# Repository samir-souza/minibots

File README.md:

</img><br> 

**minibots** is an open source and open hardware platform for experimenting with autonomous bots, Machine Learning and Programming. You can download the code and the assets to create your own fleet of bots, using a 3D printer and some basic electronic components. It is based on the ESP8266 uController, but you can modify it and use any uController you want. 
 
<br><br> 

<p align="center">
</img>
</p>

## Smart City with minibots
In this repo you will find a demo of a Smart City simulation. The idea of this demo is to use **minibots** to 
represent cars moving around on the streets of a city. There are a few places around the track like: houses, gas stations, buildings, etc.
The cars are going from on place to another, simulating a rush hour and generting traffic jams. The targets are selected randomly, and
each car automatically selects the next random target as soon as it gets to the current target place. The controller will try to 
re-route the cars to alternative paths to alleviate the traffic. You can also make the things worse by manually adding some 
obstacles to the streets, like: dogs, pedestriang, etc.
Also, there is a special marker that you can put close to a place. It will bias the next target selected by the first car that finishes the current path.  

<p align="center">
 </img>
</p> 

[Click here for more details about this demo](04_Examples/01_SmartCity)

## Components

A Minibot is composed by three modules: 1) the 3D printed parts and a few other parts; 2) the bot Printed Circuit Board (PCB); and 3) the firmware;

### 3D Models
In the first module [3D Models](01_3DModels) you will find the STL files and the FreeCAD projects used to build this project. Just follow the instructions on the module page "[3D Models](01_3DModels)" to get the files and print them.
### Bot PCB
In the second module [Bot PCB](02_BotPCB) you will find instructions about how to create the Printed Circuit Board for your Minibot. Also, you'll find the [Gerber files](https://en.wikipedia.org/wiki/Gerber_format), required for manufacturing the PCB and the components list.
### Firmware
In the third module [Firmware](03_BotFirmware) you will find the binary images and a Dockerfile that you can use to hack and customize the firmware of your Minibot. The firmware is for the uController ESP8266 and is based on Nodemcu LUA: https://nodemcu.readthedocs.io/en/master/. So, after installing the Nodemcu firmware you can customize the Lua scripts to adapt your Minibot to any project.

## Assembling
Click on [ASSEMBLING](ASSEMBLING.md) to see the instructions of how to create your own Minibot from scratch.

# License
The 3D Models and the PCB projects are released in Creative Commons Attribution-ShareAlike 4.0 License and the source code available in this repository is licensed under the GNU General Public License v3.0.

----
<div>Logo created by <a href="https://www.designevo.com/logo-maker/" title="Free Online Logo Maker">DesignEvo logo maker</a></div>

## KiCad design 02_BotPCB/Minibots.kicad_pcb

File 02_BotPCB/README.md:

## Preparing the PCB

Minibots is based on a very popular and cheap uController, the . So, the PCB is basically this uController connected to two servos (controlled by PWM) and other elements, like the classic accelerometer+gyroscope MPU6050, external pins, control LED, etc.

The PCB was created with  **v4.0.2+dfsg1-stable** and you can see the KiCad project in this directory. The Gerber files can also be found in this dir. In order to manufacture a new PCB for you Minibot, you can use the Gerber files. If you never created a PCB before, you can use some online services that you just upload the Gerber files, pay for the boards and you then receive the boards at your home. The project is very simple. It has just one layer and you can make tracks with **copper 2Oz**.

<table>
  <tr>
    <td>PCB Layout</td>
    <td>Connections</td>
    <td>Top</td>
    <td>Bottom</td>
  </tr>
  <tr>
    <td></img></td>
    <td></img></td>
    <td></img></td>
    <td></img></td>
  </tr>
</table>

As you can see above, the layout is very simple and the list of components (BOM) is:
 - D1: LED-3MM
 - P1: Pin_Header_Straight_1x03 ; LeftServo (Micro Servo 9g SG90 with 360o hack)
 - P2: Pin_Header_Straight_1x03 ; RightServo (Micro Servo 9g SG90 with 360o hack)
 - P4: Pin_Header_Straight_1x01 ; Antenna
 - P5: Pin_Header_Straight_1x03 ; Serial
 - SW1: MiniSlideSwitch ; [Switch specs](imgs/mini_switch.jpg)
 - U1: MPU6050 ; MPU6050
 - C1,C2: C_0805_HandSoldering ; 10uf
 - C3: C_0805_HandSoldering ; 1uf
 - R2: R_0805_HandSoldering ; 100k
 - U3: MSOP-8_3x3mm_Pitch0.65mm ; MCP1253
 - R1: R_0805_HandSoldering ; 100
 - P6: Pin_Header_Straight_1x02 ; VCC
 - P7: Pin_Header_Straight_1x02 ; Power
 - P3: Pin_Header_Straight_1x02 ; Flash/Ext
 - U2: ESP8266-06
 
 ### Considerations
 You need to have some soldering skills to put all the components on the board. The uController requires an SMD soldering station, but the rest of the components can be soldered by just using a normal iron.
 
 **Micro Servo 9g SG90** is a 180 degrees servo. You need to hack it to transform it into a continuous servo (360 degrees). There are tons of tutorials on the Internet teaching how to do that. Here it is an example: https://rookieelectronics.com/servohack/
 
 **MCP1253** is a power pump, it improves the battery energy utilization and also works as a power regulation. It's mandatory to keep the correct voltage (3.3v) all the time to the uController. It also works as a power isolation, given the servos are connected directly to the battery and the rest of the circuit is feed by the power pump.
 
 **ESP8266** package 04 was used in the original project, but this packaging was discontinued, so, in v02 (this version) the package 06 was used. It is easier to find on the Internet but it is more difficult to be soldered, given it requires a Rework station (SMD soldering machine with hot air).
 
 **SMD** is important to keep the size of the board in general. You can see that all the resistors and capacitors are **SMD 0805**.

 Bottom view of the Minibot after finishing the assembly in the 3D printed Chassis:  
</img>

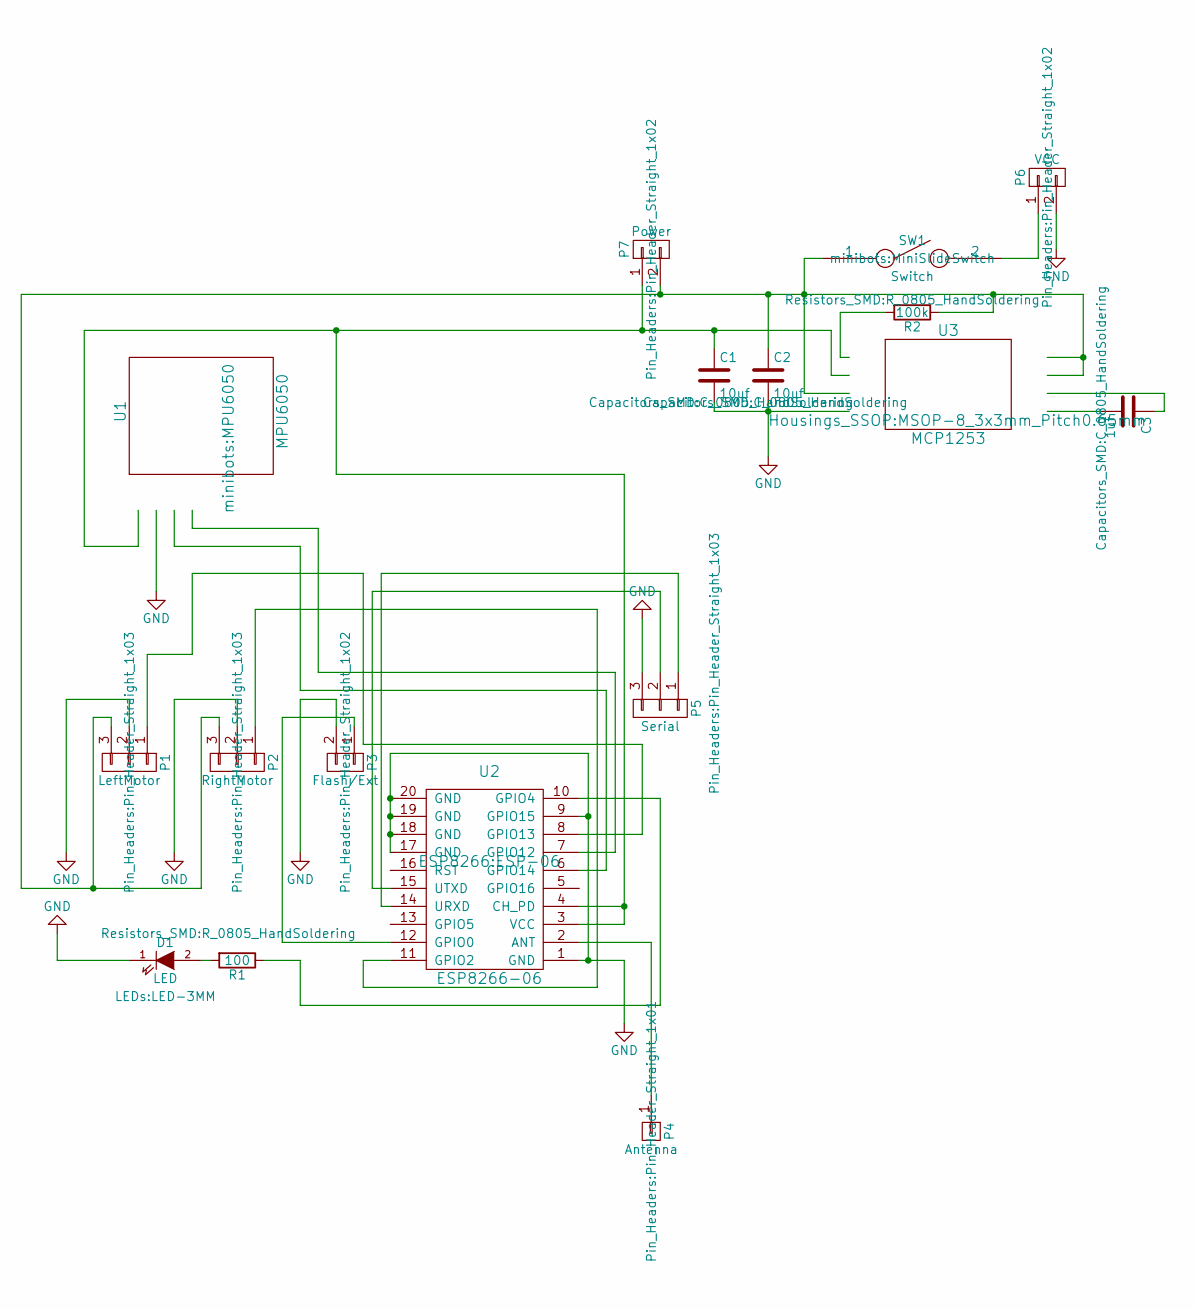
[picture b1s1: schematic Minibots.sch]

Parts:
C1, C2: 10uf; C_0805_HandSoldering
C3: 1uf; C_0805_HandSoldering
D1: LED; LED-3MM
P1: LeftMotor; Pin_Header_Straight_1x03
P2: RightMotor; Pin_Header_Straight_1x03
P3: Flash/Ext; Pin_Header_Straight_1x02
P4: Antenna; Pin_Header_Straight_1x01
P5: Serial; Pin_Header_Straight_1x03
P6: VCC; Pin_Header_Straight_1x02
P7: Power; Pin_Header_Straight_1x02
R1: 100; R_0805_HandSoldering
R2: 100k; R_0805_HandSoldering
SW1: Switch; MiniSlideSwitch
U1: MPU6050
U2: ESP8266-06; ESP-06
U3: MCP1253; MSOP-8_3x3mm_Pitch0.65mm

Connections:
GND: C1.2, C2.2, D1.1 (K), P1.2, P2.2, P3.2, P5.3, P6.2, U1.2 (GND), U2.1 (GND), U2.9 (GPIO15), U2.17 (GND), U2.18 (GND), U2.19 (GND), U2.20 (GND), U3.4 (GND)
unnamed: C1.1, P7.1, U1.1 (VCC), U2.3 (VCC), U2.4 (CH_PD), U3.2 (VOUT)
unnamed: C2.1, P1.3, P2.3, P7.2, R2.1, SW1.1, U3.3 (VIN), U3.7 (SHDN), U3.8 (SELECT)
unnamed: C3.1, U3.6 (C+)
unnamed: C3.2, U3.5 (C-)
unnamed: D1.2 (A), R1.2
unnamed: P1.1, U2.8 (GPIO13)
unnamed: P2.1, U2.11 (GPIO2)
unnamed: P3.1, U2.12 (GPIO0)
unnamed: P4.1, U2.2 (ANT)
unnamed: P5.1, U2.14 (URXD)
unnamed: P5.2, U2.15 (UTXD)
unnamed: P6.1, SW1.2
unnamed: R1.1, U2.10 (GPIO4)
unnamed: R2.2, U3.1 (PGOOD)
unnamed: U1.3 (SCL), U2.6 (GPIO14)
unnamed: U1.4 (SDA), U2.7 (GPIO12)

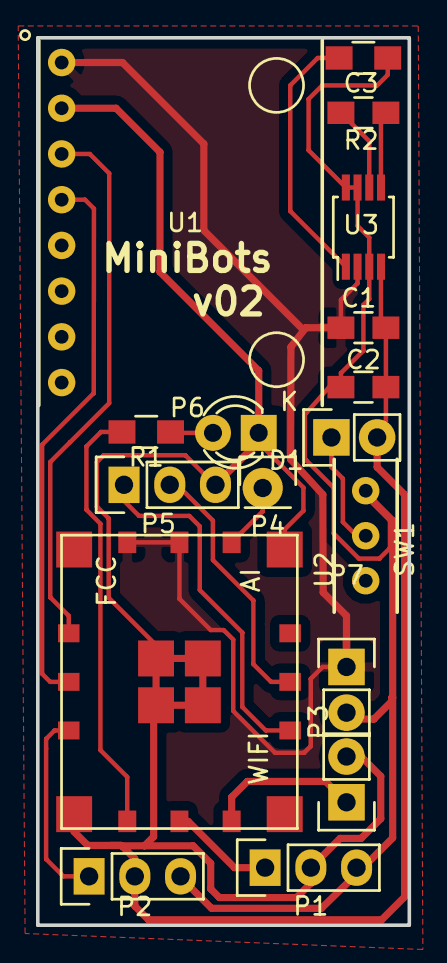
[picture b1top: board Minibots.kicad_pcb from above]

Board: 2 copper layers, 20.6 x 49.3 mm, 17 parts (0 on the bottom side), 17 nets.

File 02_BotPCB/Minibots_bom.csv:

"Id";"Designator";"Package";"Quantity";"Designation";"Supplier and ref";
1;"D1";"LED-3MM";1;"LED";;;
2;"P1";"Pin_Header_Straight_1x03";1;"LeftMotor";;;
3;"P2";"Pin_Header_Straight_1x03";1;"RightMotor";;;
4;"P4";"Pin_Header_Straight_1x01";1;"Antenna";;;
5;"P5";"Pin_Header_Straight_1x03";1;"Serial";;;
6;"SW1";"MiniSlideSwitch";1;"Switch";;;
7;"U1";"MPU6050";1;"MPU6050";;;
8;"C1,C2";"C_0805_HandSoldering";2;"10uf";;;
9;"C3";"C_0805_HandSoldering";1;"1uf";;;
10;"R2";"R_0805_HandSoldering";1;"100k";;;
11;"U3";"MSOP-8_3x3mm_Pitch0.65mm";1;"MCP1253";;;
12;"R1";"R_0805_HandSoldering";1;"100";;;
13;"P6";"Pin_Header_Straight_1x02";1;"VCC";;;
14;"P7";"Pin_Header_Straight_1x02";1;"Power";;;
15;"P3";"Pin_Header_Straight_1x02";1;"Flash/Ext";;;
16;"U2";"ESP-06";1;"ESP8266-06";;;

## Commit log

2020-08-01 - All files
2020-08-01 - fixed a bug with the login message
2020-10-22 - fix quaternion reading

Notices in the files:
02_BotPCB/Minibots.sch:
License CC BY 4.0
